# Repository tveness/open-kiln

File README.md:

# Open source kiln 

This project has grown out of the design (and hopefully construction in the near
future) of a kiln for heat-treating 80CrV2 steel.

The project is divided into two main parts: the driver circuit, and the kiln
itself. The driver circuit is assembled from readily-available modules arranged
on a custom PCB (we have a few spares and are happy to post you one of them),
whose design files and production-ready gerbers are in the repository.
The 

All designs are open: copying and improving is not only allowed, but encouraged.

## Driver circuit

### PCB

We chose to use readily available modules both for protoyping purposes, and also
so reproduction is easy: the modules can all be purchased cheaply and the whole
assembly requires only through-hole soldering skills.

The components used are:

* Wemos D1 mini ESP8266 --- logic and power for board
* MAX6675 temperature module --- converts voltage from K-type thermocouple into signal which can be processed by ESP8266
* Rotary encoder --- input with rotating left and right, and depressing
* 0.96" TFT display
* 3x 5V relay modules

Some of these modules may come with headers already soldered, in which case you
may have to desolder and re-solder appropriate headers (all headers on PCB are
2.54mm/0.1" headers).

The PCB was designed with Kicad.

The logic of the design is that the temperature module measures the temperature
inside the kiln, and then according to the settings (TFT + rotary encoder
interface) the relays are activated to regulate the kiln temperature.

### Software

## Physical kiln

### Materials
We will need 27 vermiculite bricks for the main oven. 

### Firebrick enclosure
This is to be made from vermiculite firebricks. These are supplied in Imperial measurements; each brick has dimension:
$$ 8 \times 1 \times 4 ''.$$
The firebrick enclosure is to consist of two parts: the oven cavity, and a door. The measurements of these are as follows:

**Oven**:
Interior: $16 \times 8 \times 6''$

Exterior: $10 \times 17 \times 8$

**Door**:
The door is to be two bricks thick. The dimensions are:
$2 \times 10 \times 8$.

### Plaster casing
The plan is to cast a set of thick sheets with which to encase the oven. Since the door will be two bricks thick, there will be no outer casing for the door. The dimensions for these are to be:

Walls($\times 2$): $17 \times 10 \times d$

floor / ceiling ($\times 2$): $(17+d)\times(8+2d)\times d$

back ($\times 1$): $(8 + 2d)\times 10\times d$

where $d$ gives the thickness for the sheets. Provisionally, this is set at $1.5$''. 

### Approach 1:
Mix vermiculite to quick-set cement in a ratio $4:1$, add water until you can squeeze a fist and get a few drops out. 

### Metal case

### Resistive Elements
We use A1 kanthal wire, sourced from [here](https://www.ebay.co.uk/itm/322024532921). This has a resistivity of $1.8\Omega / m$. Aiming for $R = 13.2 \Omega$ per coil, we calculate:
$$d = 13.2 / 1.8 \\ = 7.3 $$
So that each element ought to be 7.3 $m$ long. 

### Wiring diagram
These images temporary, to be replaced

### Safety considerations
We are to use:
- MCBs on each resistor element to isolate those in case of a short circuit. Also if one of the other coils fails, the power draw on the remaining coils would increase - the MCB here would save those coils before they burn out.
- Magnetic switch; this will leave a circuit *open* when the oven door is open, and *closed* when the oven door is closed. This means that there should be no power to the heating elements when the door is open. 
- Connector: This would function as a relay switch for the three phase power
- Relay: This would act as a pre-relay, and would be controlled directly by the PCB. (Expand this section)

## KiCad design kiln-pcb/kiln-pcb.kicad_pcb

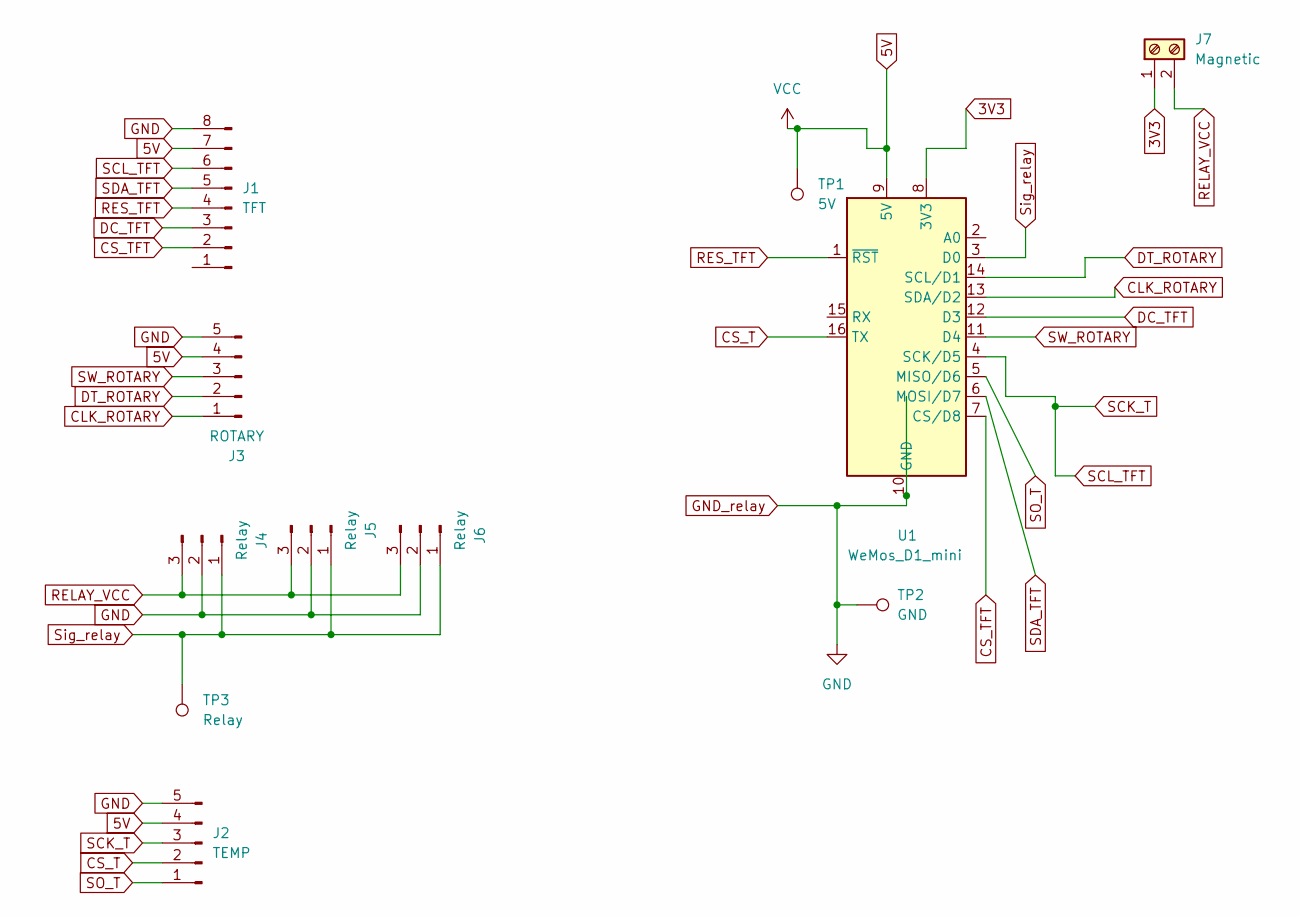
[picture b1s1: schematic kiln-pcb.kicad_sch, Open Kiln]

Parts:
J1: TFT; PinHeader_1x08_P2.54mm_Vertical
J2: TEMP; PinHeader_1x05_P2.54mm_Vertical
J3: ROTARY; PinHeader_1x05_P2.54mm_Vertical
J4, J5, J6: Relay; PinHeader_1x03_P2.54mm_Vertical
J7: Magnetic; TerminalBlock_bornier-2_P5.08mm
TP1: 5V; TestPoint_Pad_D2.0mm
TP2: GND; TestPoint_Pad_D2.0mm
TP3: Relay; TestPoint_Pad_D2.0mm
U1: WeMos_D1_mini; WEMOS_D1_mini_light

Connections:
3V3: J7.1, U1.8 (3V3); also elsewhere on the board
5V: J1.7, J2.4, J3.4, TP1.1, U1.9 (5V)
CLK_ROTARY: J3.1, U1.13 (SDA/D2)
CS_T: J2.2, U1.16 (TX)
CS_TFT: J1.2, U1.7 (CS/D8)
DC_TFT: J1.3, U1.12 (D3)
DT_ROTARY: J3.2, U1.14 (SCL/D1)
GND: J1.8, J2.5, J3.5, J4.2, J5.2, J6.2, TP2.1, U1.10 (GND)
RELAY_VCC: J4.3, J5.3, J6.3, J7.2; also elsewhere on the board
RES_TFT: J1.4, U1.1 (~RST)
SCK_T: J1.6, J2.3, U1.4 (SCK/D5)
SDA_TFT: J1.5, U1.6 (MOSI/D7)
SO_T: J2.1, U1.5 (MISO/D6)
SW_ROTARY: J3.3, U1.11 (D4)
Sig_relay: J4.1, J5.1, J6.1, TP3.1, U1.3 (D0)

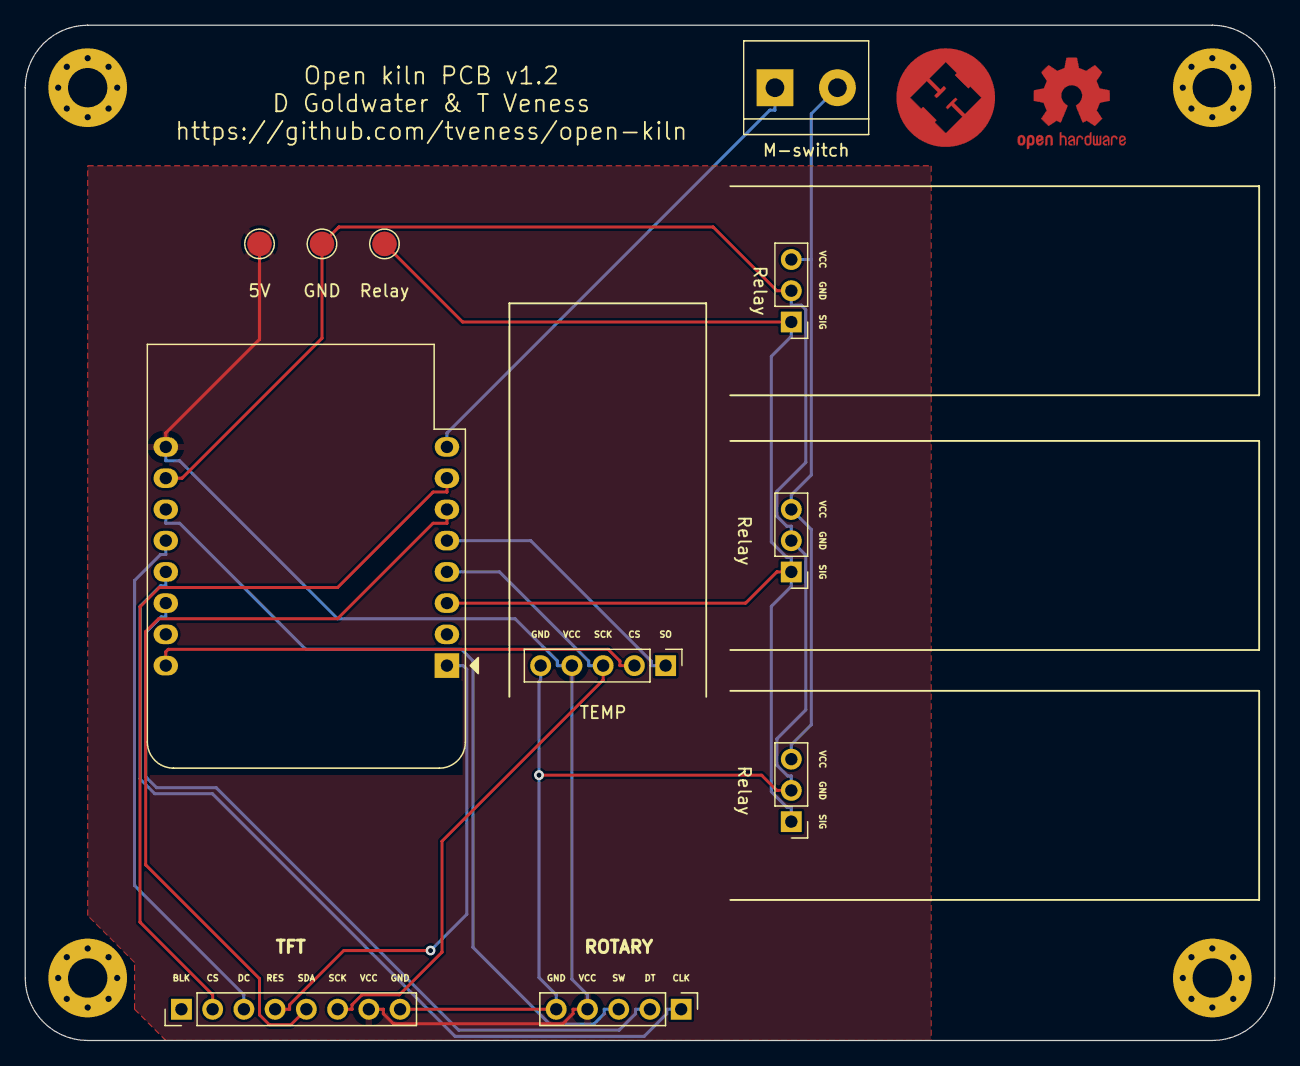
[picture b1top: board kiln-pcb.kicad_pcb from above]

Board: 2 copper layers, 101.6 x 82.6 mm, 17 parts (0 on the bottom side), 15 nets.

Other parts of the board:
H1, H2, H3, H4: MountingHole_3.2mm_M3_Pad_Via
HS_LOGO: Val**; hackspace_small
M-switch: Magnetic; TerminalBlock_bornier-2_P5.08mm
OSHW_LOGO: OSHW-Logo2_9.8x8mm_Copper

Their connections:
3V3: M-switch.1; also elsewhere on the board
RELAY_VCC: M-switch.2; also elsewhere on the board

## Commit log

2022-06-07 Added simple PID for relay
2022-06-11 PCB v1.1
2022-06-11 Fixed "kerning"
2022-06-11 Basic README update
2022-06-11 Assembled pic
2022-06-12 Added magnetic switch interrupt
2022-06-15 New PCB image
2022-06-19 Added basic dimensions and resistor specs
